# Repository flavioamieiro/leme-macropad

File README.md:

## Leme macropad

This is a macropad based on the RP2040 microcontroller meant to run QMK.

It currently is a handwired macropad using a raspberry Pi pico

The [README in the software directory](software/README.md) explains how to install QMK on a raspberry pi pico to support it.

The [leme_macropad](leme_macropad/) directory contains a first revision for custom hardware for it (which, unfortunately, currently doesn't work).

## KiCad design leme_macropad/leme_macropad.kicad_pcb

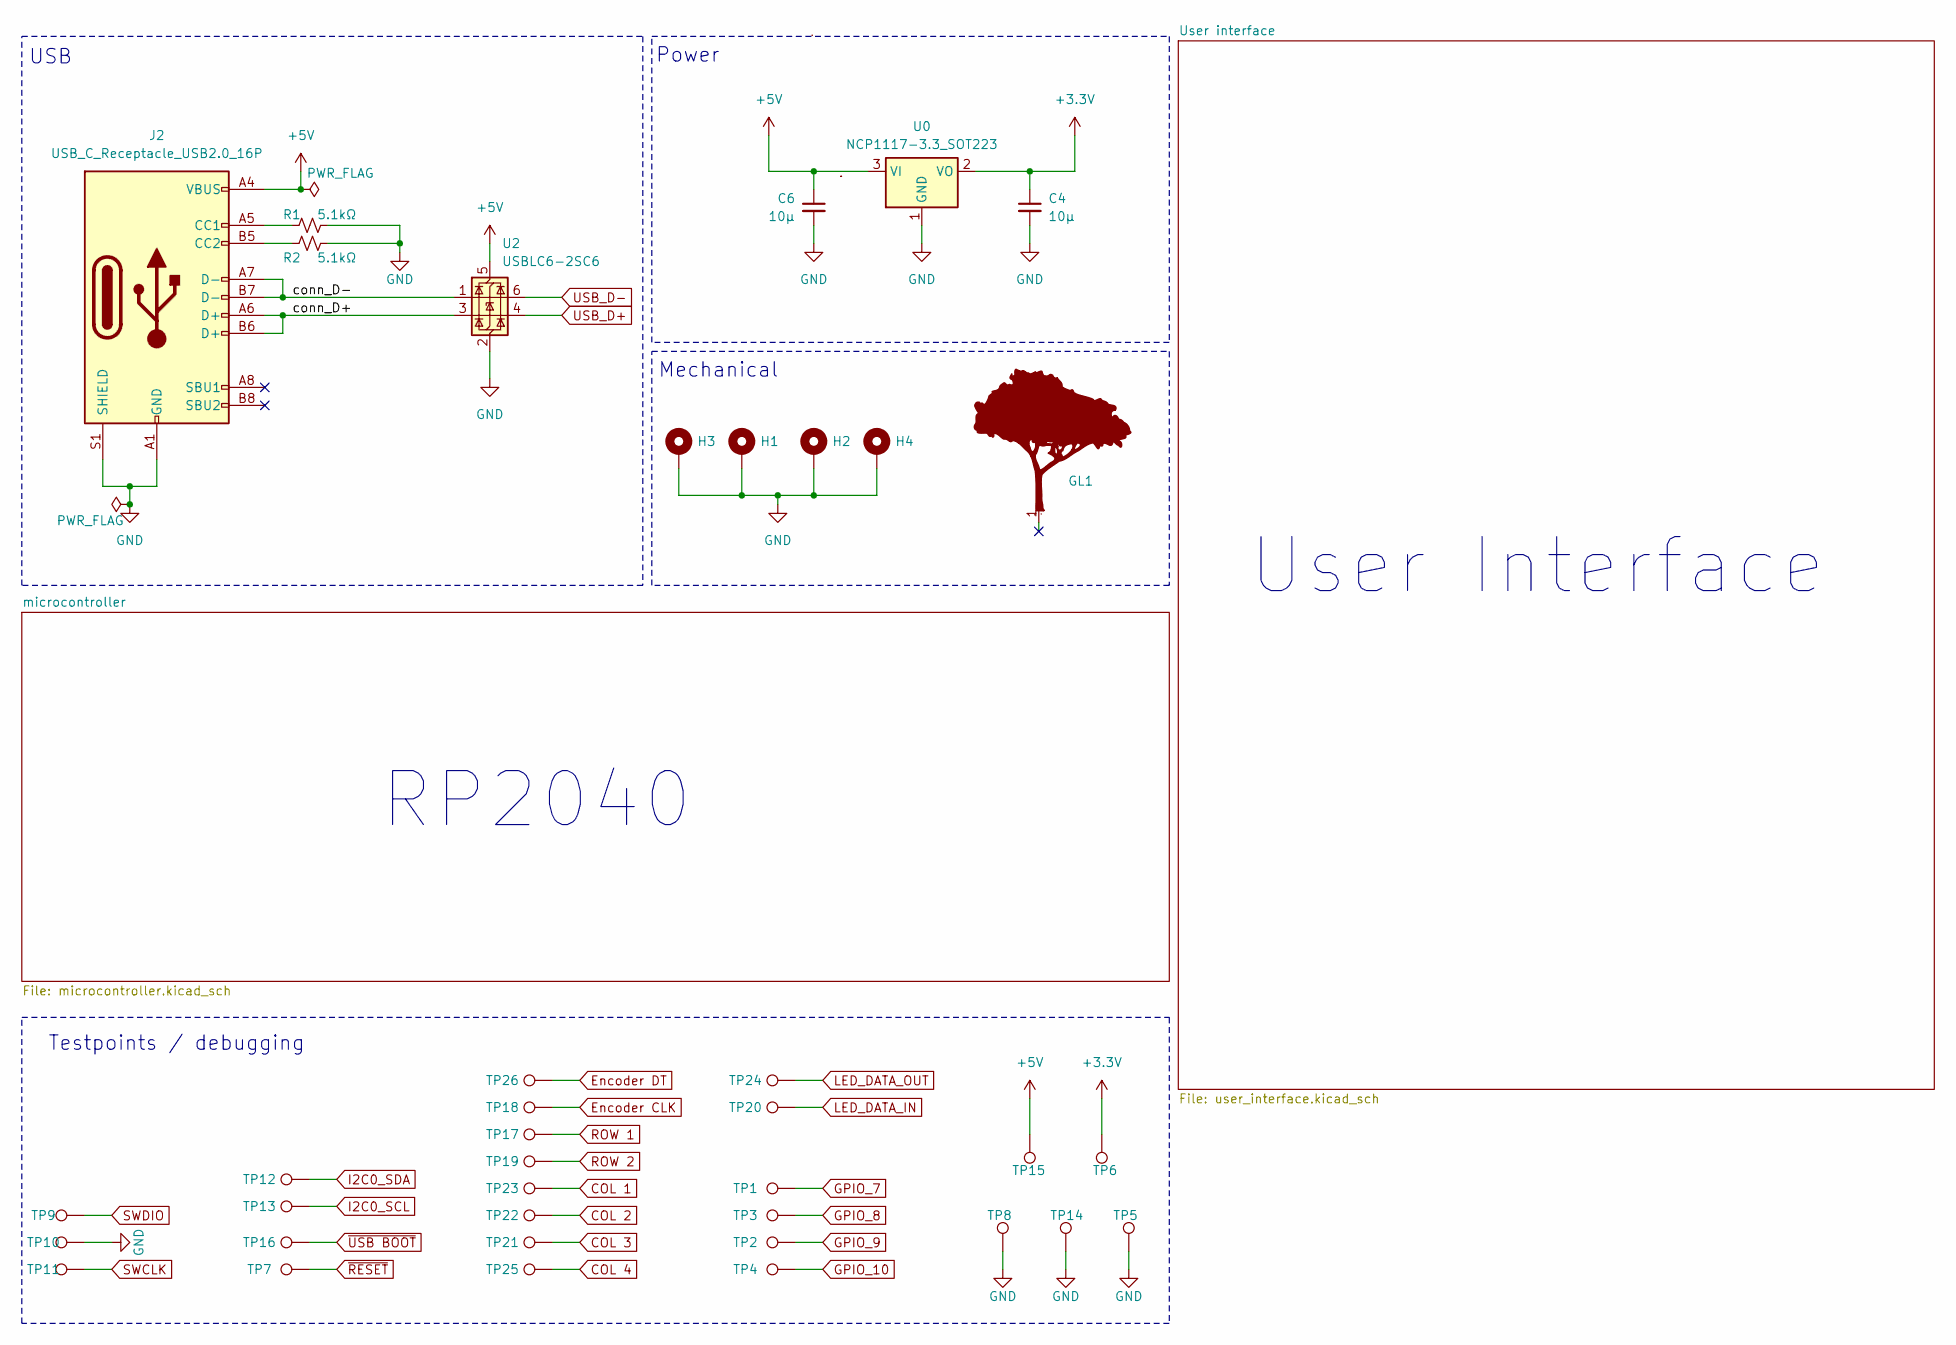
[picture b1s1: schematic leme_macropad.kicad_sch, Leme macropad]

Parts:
C4, C6: 10μ; C_0402_1005Metric_Pad0.74x0.62mm_HandSolder
GL1: ipe_logo
H1, H2, H3, H4: MountingHole_Pad; MountingHole_2.2mm_M2_Pad
J2: USB_C_Receptacle_USB2.0_16P; USB_C_Receptacle_GCT_USB4105-xx-A_16P_TopMnt_Horizontal
R1, R2: 5.1kΩ; R_0402_1005Metric_Pad0.72x0.64mm_HandSolder
TP1, TP2, TP3, TP4, TP5, TP6, TP7, TP8, TP9, TP10, TP11, TP12, TP13, TP14, TP15, TP16, TP17, TP18, TP19, TP20, TP21, TP22, TP23, TP24, TP25, TP26: TestPoint; TestPoint_Pad_D1.0mm
U0: NCP1117-3.3_SOT223; SOT-223-3_TabPin2
U2: USBLC6-2SC6; SOT-23-6

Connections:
+3.3V: C4.1, TP6.1, U0.2 (VO); also elsewhere on the board
+5V: C6.1, J2.A4 (VBUS), J2.A9 (VBUS), J2.B4 (VBUS), J2.B9 (VBUS), TP15.1, U0.3 (VI), U2.5 (VBUS); also elsewhere on the board
/conn_D+: J2.A6 (D+), J2.B6 (D+), U2.3 (I/O2)
/conn_D-: J2.A7 (D-), J2.B7 (D-), U2.1 (I/O1)
COL 1: TP23.1; also elsewhere on the board
COL 2: TP22.1; also elsewhere on the board
COL 3: TP21.1; also elsewhere on the board
COL 4: TP25.1; also elsewhere on the board
Encoder CLK: TP18.1; also elsewhere on the board
Encoder DT: TP26.1; also elsewhere on the board
GND: C4.2, C6.2, H1.1, H2.1, H3.1, H4.1, J2.A1 (GND), J2.A12 (GND), J2.B1 (GND), J2.B12 (GND), J2.S1 (SHIELD), R1.2, R2.2, TP5.1, TP8.1, TP10.1, TP14.1, U0.1 (GND), U2.2 (GND); also elsewhere on the board
GPIO_7: TP1.1; also elsewhere on the board
GPIO_8: TP3.1; also elsewhere on the board
GPIO_9: TP2.1; also elsewhere on the board
GPIO_10: TP4.1; also elsewhere on the board
I2C0_SCL: TP13.1; also elsewhere on the board
I2C0_SDA: TP12.1; also elsewhere on the board
LED_DATA_IN: TP20.1; also elsewhere on the board
LED_DATA_OUT: TP24.1; also elsewhere on the board
unnamed: J2.A5 (CC1), R1.1
unnamed: J2.B5 (CC2), R2.1
ROW 1: TP17.1; also elsewhere on the board
ROW 2: TP19.1; also elsewhere on the board
SWCLK: TP11.1; also elsewhere on the board
SWDIO: TP9.1; also elsewhere on the board
USB_D+: U2.4 (I/O2); also elsewhere on the board
USB_D-: U2.6 (I/O1); also elsewhere on the board
~RESET: TP7.1; also elsewhere on the board
~USB BOOT: TP16.1; also elsewhere on the board

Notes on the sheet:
Mechanical
User Interface
USB
RP2040
Testpoints / debugging
Power

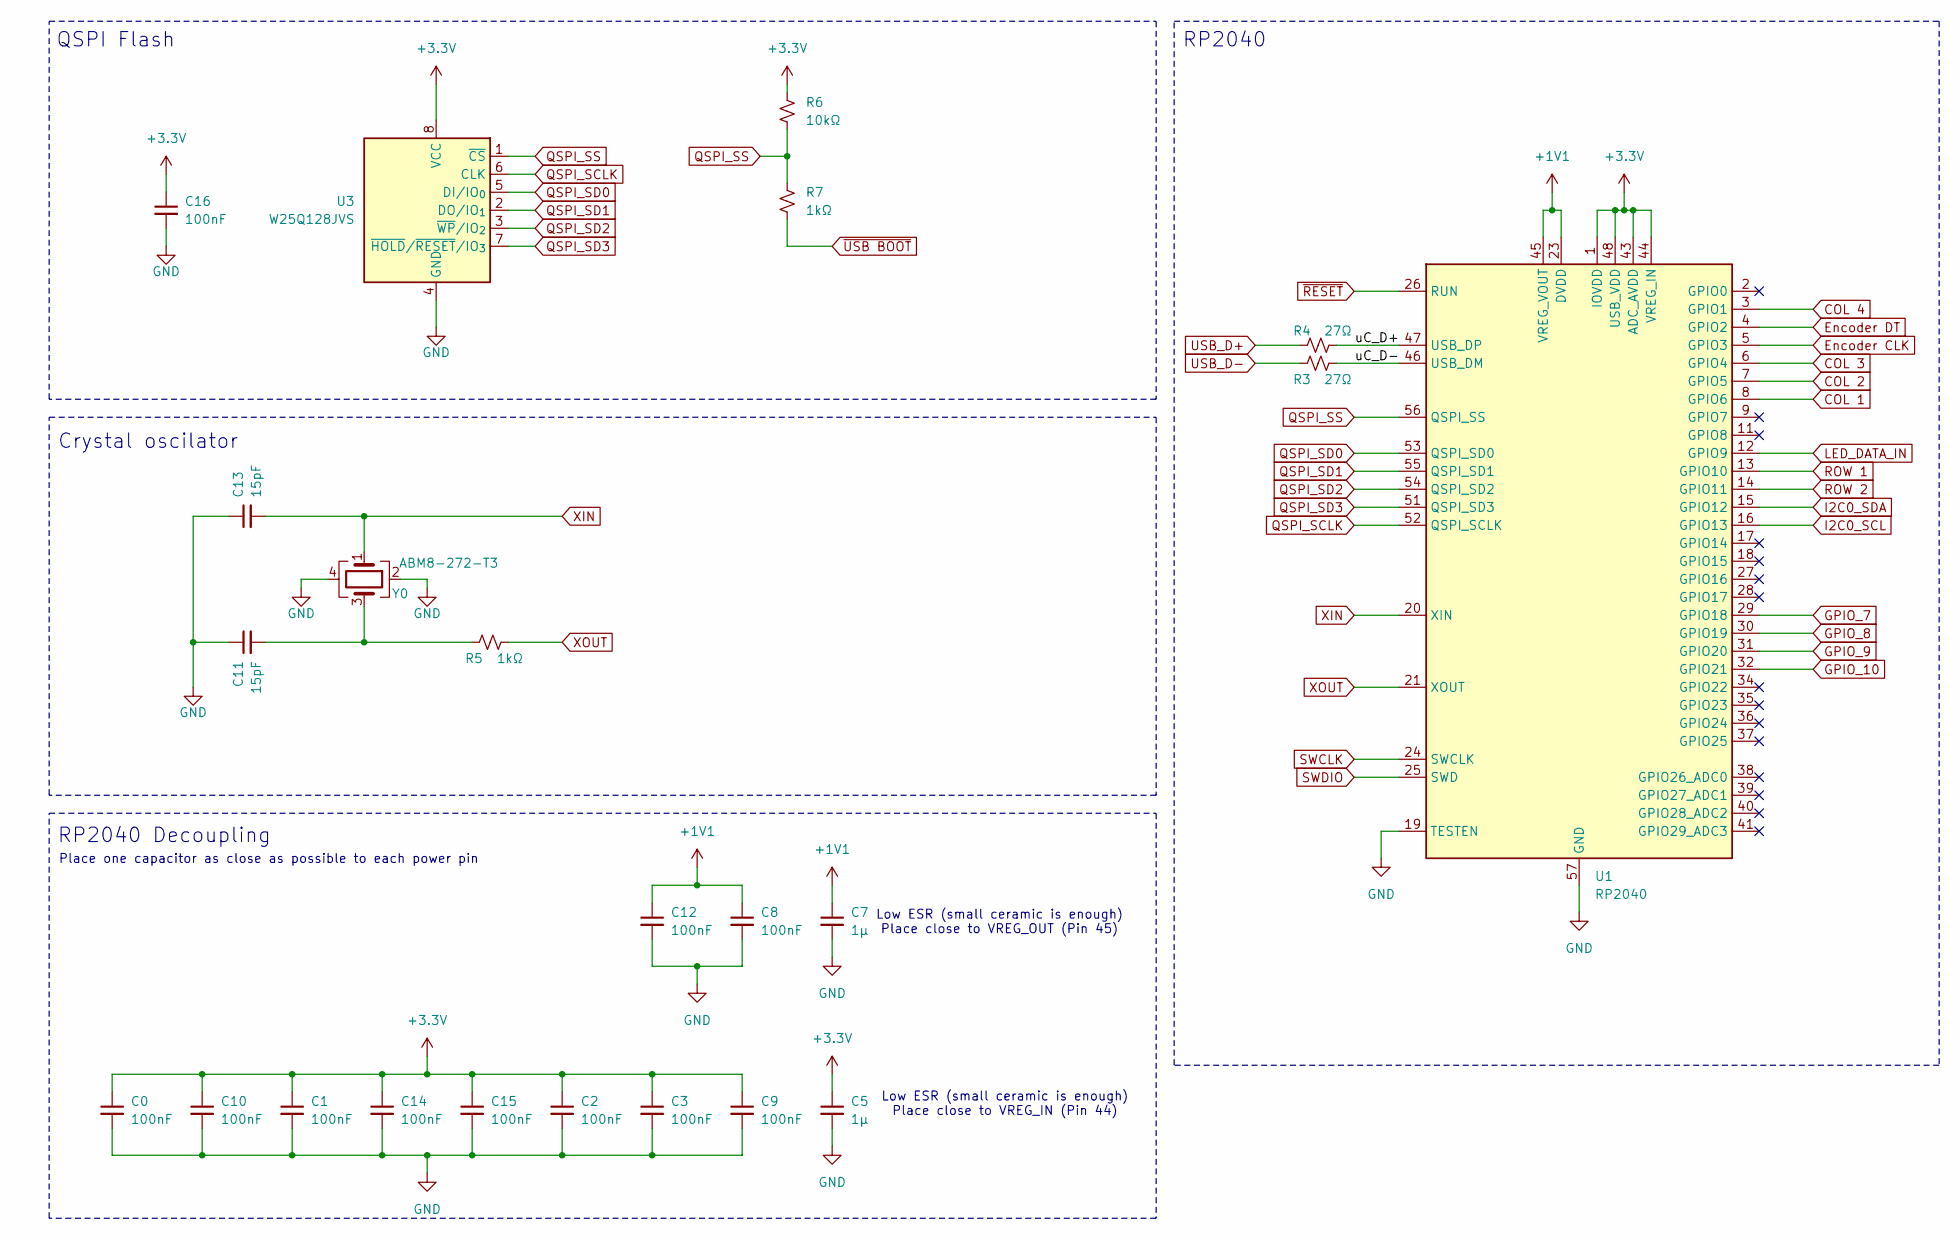
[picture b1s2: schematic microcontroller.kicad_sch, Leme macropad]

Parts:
C0, C1, C2, C3, C8, C9, C10, C12, C14, C15, C16: 100nF; C_0402_1005Metric_Pad0.74x0.62mm_HandSolder
C5, C7: 1μ; C_0402_1005Metric_Pad0.74x0.62mm_HandSolder
C11, C13: 15pF; C_0402_1005Metric_Pad0.74x0.62mm_HandSolder
R3, R4: 27Ω; R_0402_1005Metric_Pad0.72x0.64mm_HandSolder
R5, R7: 1kΩ; R_0402_1005Metric_Pad0.72x0.64mm_HandSolder
R6: 10kΩ; R_0402_1005Metric_Pad0.72x0.64mm_HandSolder
U1: RP2040; QFN-56-1EP_7x7mm_P0.4mm_EP3.2x3.2mm
U3: W25Q128JVS; SOIC-8_5.3x5.3mm_P1.27mm
Y0: ABM8-272-T3; Crystal_SMD_3225-4Pin_3.2x2.5mm

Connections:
+1V1: C7.1, C8.1, C12.1, U1.23 (DVDD), U1.45 (VREG_VOUT), U1.50 (DVDD)
+3.3V: C0.1, C1.1, C2.1, C3.1, C5.1, C9.1, C10.1, C14.1, C15.1, C16.1, R6.2, U1.1 (IOVDD), U1.10 (IOVDD), U1.22 (IOVDD), U1.33 (IOVDD), U1.42 (IOVDD), U1.43 (ADC_AVDD), U1.44 (VREG_IN), U1.48 (USB_VDD), U1.49 (IOVDD), U3.8 (VCC); also elsewhere on the board
/microcontroller/uC_D+: R4.2, U1.47 (USB_DP)
/microcontroller/uC_D-: R3.2, U1.46 (USB_DM)
COL 1: U1.8 (GPIO6); also elsewhere on the board
COL 2: U1.7 (GPIO5); also elsewhere on the board
COL 3: U1.6 (GPIO4); also elsewhere on the board
COL 4: U1.3 (GPIO1); also elsewhere on the board
Encoder CLK: U1.5 (GPIO3); also elsewhere on the board
Encoder DT: U1.4 (GPIO2); also elsewhere on the board
GND: C0.2, C1.2, C2.2, C3.2, C5.2, C7.2, C8.2, C9.2, C10.2, C11.1, C12.2, C13.1, C14.2, C15.2, C16.2, U1.19 (TESTEN), U1.57 (GND), U3.4 (GND), Y0.2, Y0.4; also elsewhere on the board
GPIO_7: U1.29 (GPIO18); also elsewhere on the board
GPIO_8: U1.30 (GPIO19); also elsewhere on the board
GPIO_9: U1.31 (GPIO20); also elsewhere on the board
GPIO_10: U1.32 (GPIO21); also elsewhere on the board
I2C0_SCL: U1.16 (GPIO13); also elsewhere on the board
I2C0_SDA: U1.15 (GPIO12); also elsewhere on the board
LED_DATA_IN: U1.12 (GPIO9); also elsewhere on the board
unnamed: C11.2, R5.1, Y0.3
QSPI_SCLK: U1.52 (QSPI_SCLK), U3.6 (CLK)
QSPI_SD0: U1.53 (QSPI_SD0), U3.5 (DI/IO_{0})
QSPI_SD1: U1.55 (QSPI_SD1), U3.2 (DO/IO_{1})
QSPI_SD2: U1.54 (QSPI_SD2), U3.3 (~WP/IO_{2})
QSPI_SD3: U1.51 (QSPI_SD3), U3.7 (~HOLD/~RESET/IO_{3})
QSPI_SS: R6.1, R7.2, U1.56 (QSPI_SS), U3.1 (~CS)
ROW 1: U1.13 (GPIO10); also elsewhere on the board
ROW 2: U1.14 (GPIO11); also elsewhere on the board
SWCLK: U1.24 (SWCLK); also elsewhere on the board
SWDIO: U1.25 (SWD); also elsewhere on the board
USB_D+: R4.1; also elsewhere on the board
USB_D-: R3.1; also elsewhere on the board
XIN: C13.2, U1.20 (XIN), Y0.1
XOUT: R5.2, U1.21 (XOUT)
~RESET: U1.26 (RUN); also elsewhere on the board
~USB BOOT: R7.1; also elsewhere on the board

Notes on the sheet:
RP2040 Decoupling
Place one capacitor as close as possible to each power pin
QSPI Flash
RP2040
Low ESR (small ceramic is enough) Place close to VREG_OUT (Pin 45)
Low ESR (small ceramic is enough) Place close to VREG_IN (Pin 44)
Crystal oscilator

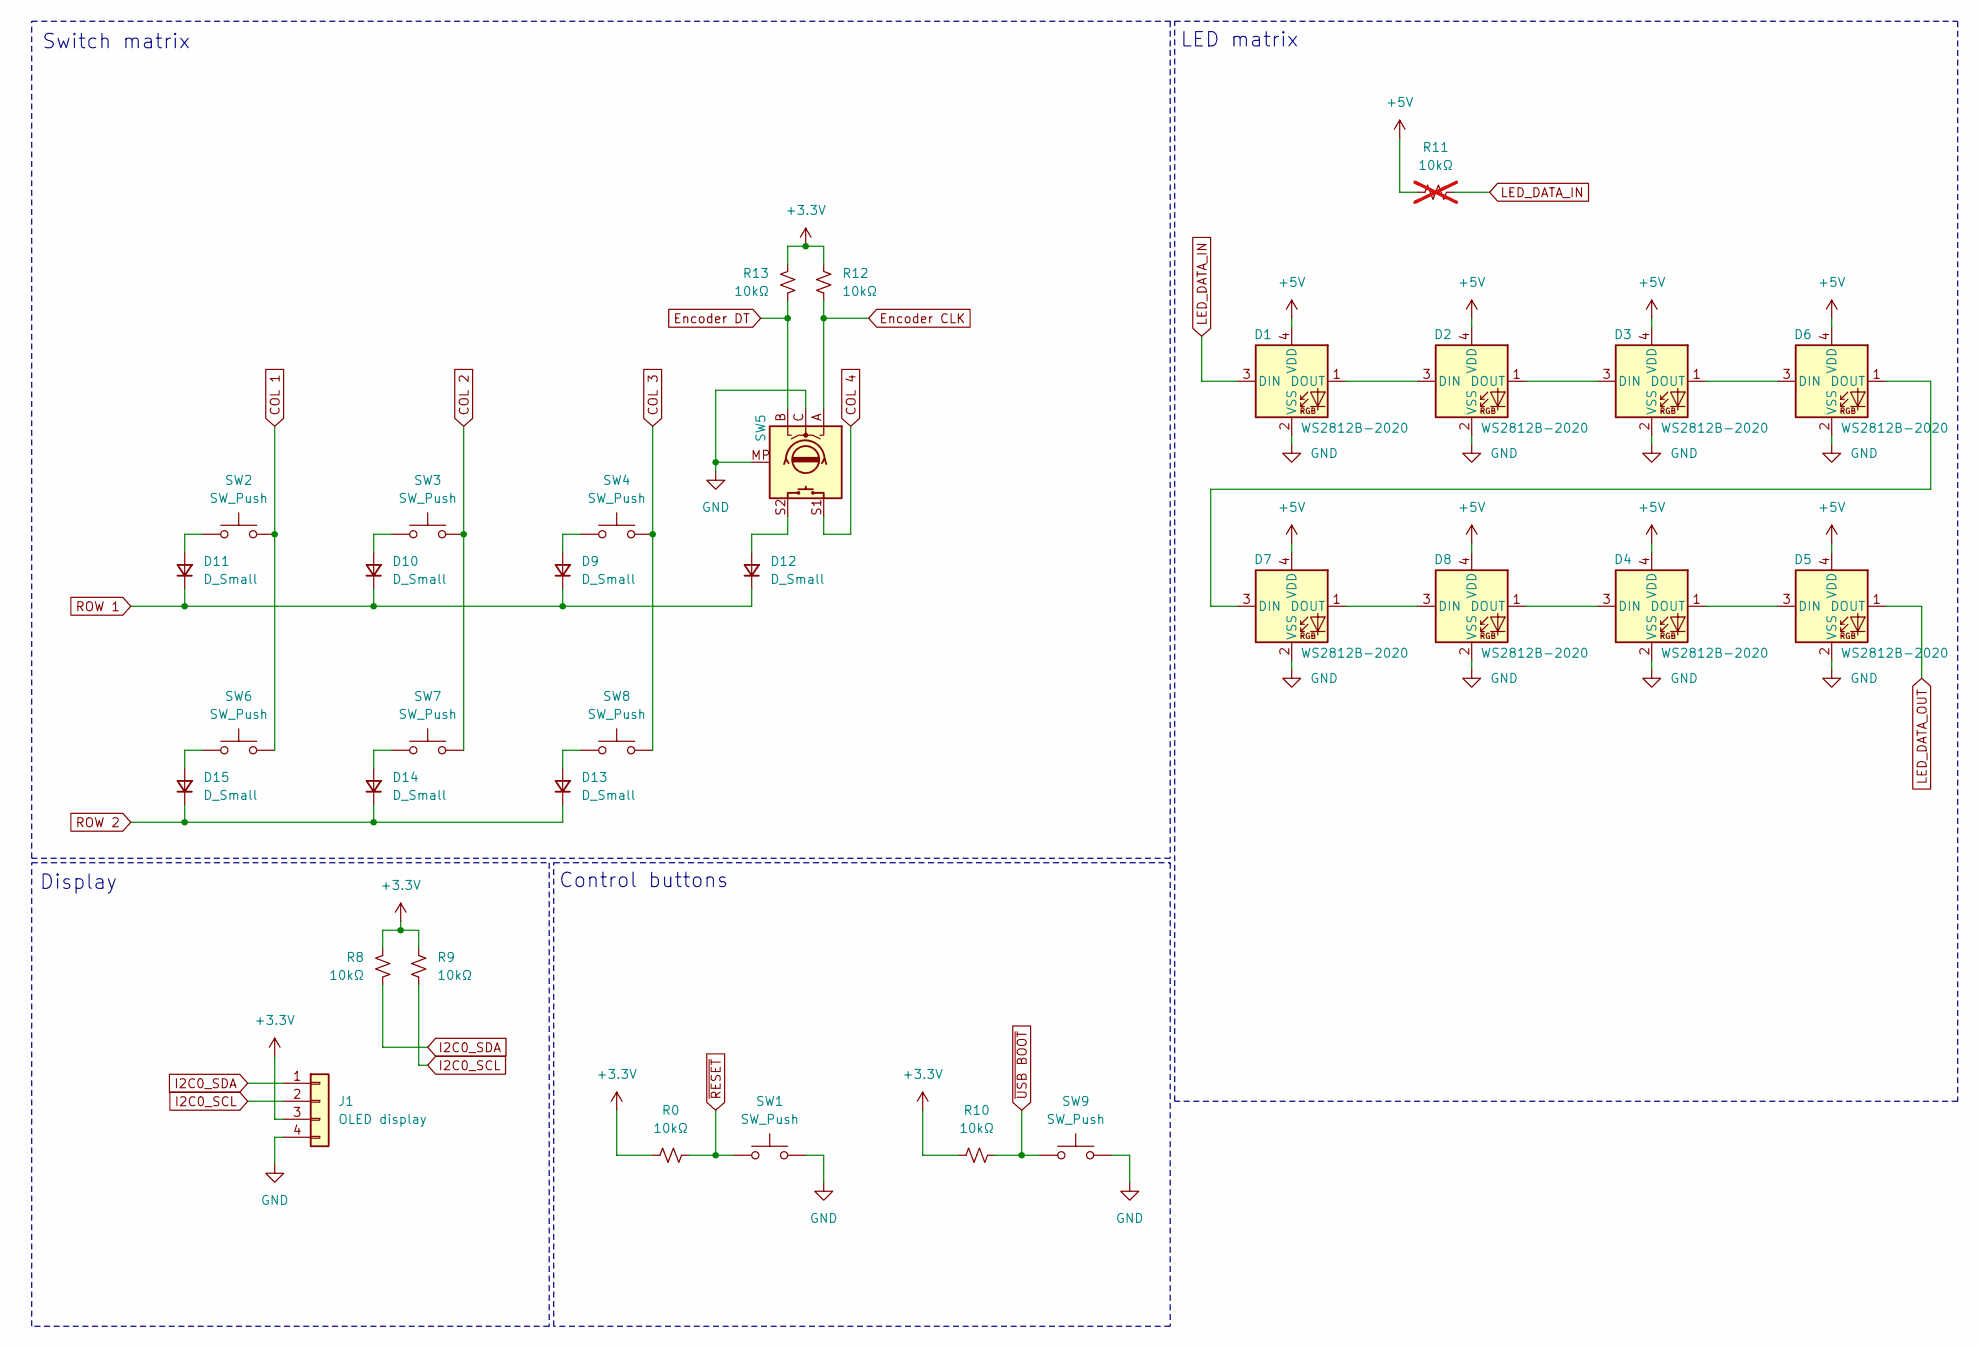
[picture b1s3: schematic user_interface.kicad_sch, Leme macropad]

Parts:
D1, D2, D3, D4, D5, D6, D7, D8: WS2812B-2020; LED_WS2812B-2020_PLCC4_2.0x2.0mm
D9, D10, D11, D12, D13, D14, D15: D_Small; D_SOD-123
J1: OLED display; PinHeader_1x04_P2.54mm_Vertical
R0, R8, R9, R10, R12, R13: 10kΩ; R_0402_1005Metric_Pad0.72x0.64mm_HandSolder
R11: 10kΩ; R_0402_1005Metric_Pad0.72x0.64mm_HandSolder; not fitted
SW1, SW9: SW_Push; CK_PTS636_SK43_SMTR_LFS
SW2, SW3, SW4, SW6, SW7, SW8: SW_Push; SW_Hotswap_Kailh_Choc_V1V2_1.00u
SW5: RotaryEncoder_Switch; RotaryEncoder_Alps_EC11E-Switch_Vertical_H20mm

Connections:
+3.3V: J1.3, R0.1, R8.2, R9.2, R10.1, R12.2, R13.2; also elsewhere on the board
+5V: D1.4 (VDD), D2.4 (VDD), D3.4 (VDD), D4.4 (VDD), D5.4 (VDD), D6.4 (VDD), D7.4 (VDD), D8.4 (VDD), R11.1; also elsewhere on the board
COL 1: SW2.2, SW6.2; also elsewhere on the board
COL 2: SW3.2, SW7.2; also elsewhere on the board
COL 3: SW4.2, SW8.2; also elsewhere on the board
COL 4: SW5.S1; also elsewhere on the board
Encoder CLK: R12.1, SW5.A; also elsewhere on the board
Encoder DT: R13.1, SW5.B; also elsewhere on the board
GND: D1.2 (VSS), D2.2 (VSS), D3.2 (VSS), D4.2 (VSS), D5.2 (VSS), D6.2 (VSS), D7.2 (VSS), D8.2 (VSS), J1.4, SW1.2, SW5.C, SW5.MP, SW9.2; also elsewhere on the board
I2C0_SCL: J1.2, R9.1; also elsewhere on the board
I2C0_SDA: J1.1, R8.1; also elsewhere on the board
LED_DATA_IN: D1.3 (DIN), R11.2; also elsewhere on the board
LED_DATA_OUT: D5.1 (DOUT); also elsewhere on the board
unnamed: D1.1 (DOUT), D2.3 (DIN)
unnamed: D2.1 (DOUT), D3.3 (DIN)
unnamed: D3.1 (DOUT), D6.3 (DIN)
unnamed: D4.3 (DIN), D8.1 (DOUT)
unnamed: D4.1 (DOUT), D5.3 (DIN)
unnamed: D6.1 (DOUT), D7.3 (DIN)
unnamed: D7.1 (DOUT), D8.3 (DIN)
unnamed: D9.2 (A), SW4.1
unnamed: D10.2 (A), SW3.1
unnamed: D11.2 (A), SW2.1
unnamed: D12.2 (A), SW5.S2
unnamed: D13.2 (A), SW8.1
unnamed: D14.2 (A), SW7.1
unnamed: D15.2 (A), SW6.1
ROW 1: D9.1 (K), D10.1 (K), D11.1 (K), D12.1 (K); also elsewhere on the board
ROW 2: D13.1 (K), D14.1 (K), D15.1 (K); also elsewhere on the board
~RESET: R0.2, SW1.1; also elsewhere on the board
~USB BOOT: R10.2, SW9.1; also elsewhere on the board

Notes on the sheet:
Control buttons
Switch matrix
LED matrix
Display

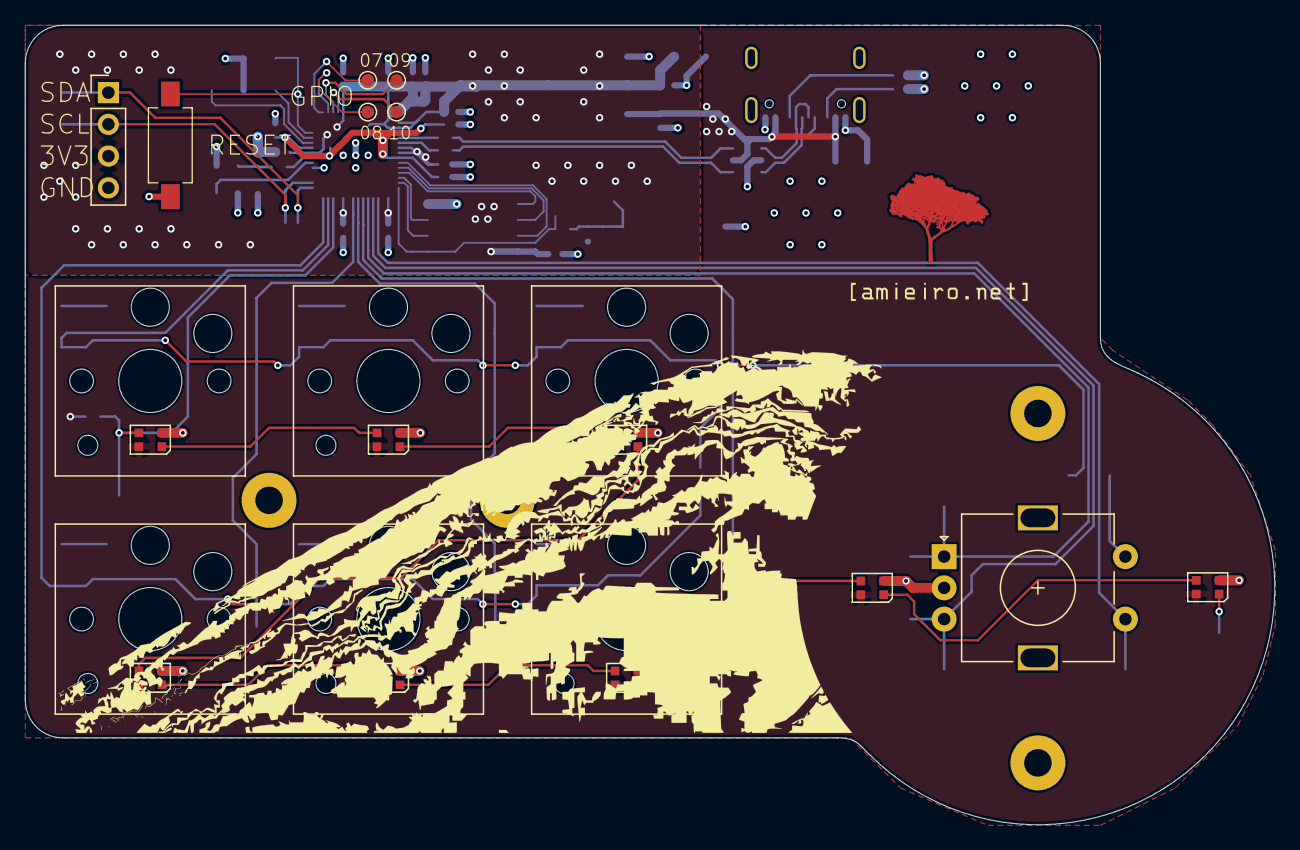
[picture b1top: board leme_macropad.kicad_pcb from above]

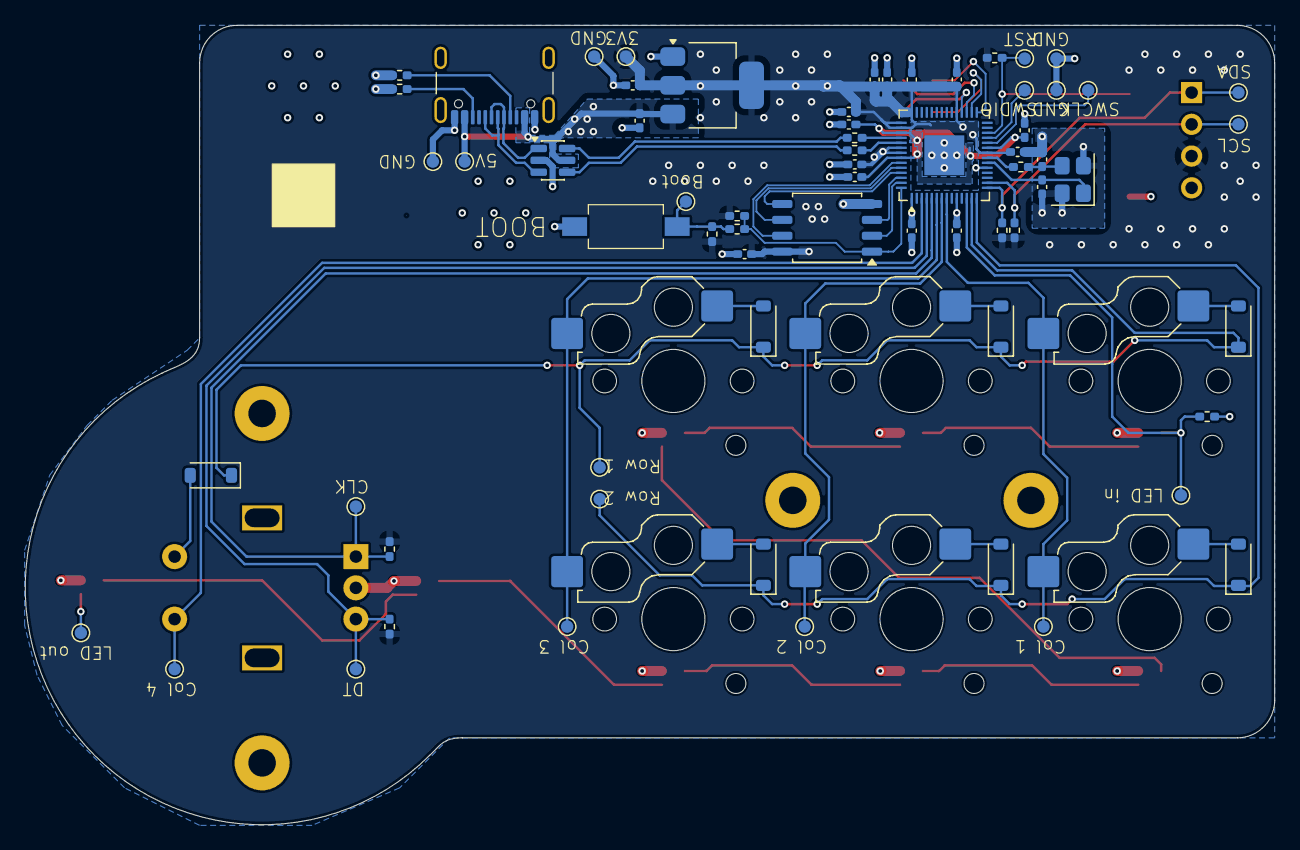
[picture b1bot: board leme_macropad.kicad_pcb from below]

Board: 4 copper layers, 99.9 x 63.9 mm, 94 parts (67 on the bottom side), 55 nets.

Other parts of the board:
Ref**: Val**; sea

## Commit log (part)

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2024-07-22 Adds first version of the code for a breadboad single button prototype
    This first prototype includes a rotary encoder and an i2c OLED display
    but only one single button. The idea was to test one of each component.
2024-07-26 Adds start of schematics and update code for perfboard prototype
    This schematics is limited only to what is in the perfboard. The code
    now also reflects the way the perfboard is wired.
2024-08-01 Adds Freecad project with a first case design
    This case design is meant to test the form factor. It doesn't fit the
    current electronics, since they were prototyped in a rather large
    perfboard. In it's current form, it can't be hardwired either, since
    there is no space for the Pi Pico inside.
2024-08-09 Finished first version of the case design
    This includes a bottom with a space for the raspberry pi pico.
    There are a few issues, mainly there's not enough space for all the
    wires (with JST connectors) I used in the prototype because one of the
    connectors hits the back of the display.
2024-08-12 Adds second layer with encoder as mouse scroll
2024-08-12 Changes col pins order for new handwired prototype
2025-04-20 Updates kicad project to kicad version 9.0
2025-04-21 Changes firmware to use QMK instead of KMK
    This QMK firmware is still very limited in comparrison to what was
    available with KMK.
    * It still has only one layer
    * The rotary encoder pushbutton doesn't work yet
    * The display is not yet included
2025-04-21 Enables ENCODER_MAP in keymap
    This allows us to describe keycode mappings for encoders in the same
    way we do for the keyboard matrix.
2025-04-21 Cleans the readme file for the keyboard
2025-04-21 Fixes copyright statement in keymaps.c
2025-04-21 Adds second layer to the macropad
    This has the same keycodes used in the previous KMK firmware, which
    means the second layer is only useful to change the rotary encoder into
    a mouse wheel instead of a volume knob. This layer should be expanded
    for more navigation helpers, and this is why I named it as `NAVIGATION`.
2025-04-21 Explains how to flash the software in README.md
2025-04-24 Adds support for OLED display
    This display uses I2C0 in the RPi with SDA on GP4 and SCL on GP5
2025-04-24 Fixes whitespace in rules.mk
2025-04-24 Adds scrolling and fade out to OLED screen
    The scrolling helps avoid burn-in on the screen, and the fade out just
    looks better.
    This commit also decreases the time it takes to clear the screen.
2025-04-24 Adds shortcut key in second layer to put the keyboard in bootloader mode
    This makes it much easier to test code, but should probably be removed
    later.
2025-05-13 Renames kicad project
2025-05-16 Uses rotary encoder instead of module and includes switch in matrix
    The way QMK handles rotary encoder push buttons is to include it in the
    switch matrix, which means I needed to add another column. Since this
    opens space for an extra switch, I added it here, but it doesn't need to
    be a mechanical switch as the others. We can keep the same 3x2 layout of
    the main keys.
    Using the encoder instead of a module is the right way to go. The
2025-05-16 Removes old Pi Pico library from the project
    We can use the official Kicad symbol and footprint for the RP2040 we'll
    use.
2025-05-16 Replaces Pi pico with a RP2040
    This is much better for our purposes. It gives us more control, uses
    much less space on the PCB and allows us to use a USB-C connector.
    All the components around the RP2040 are the ones recommended in the
    RP2040 hardware design guide. They not only are recommended, but also
    readily available and easy enough to use.
2025-05-23 Moves user interface to it's own hierarchical sheet
2025-05-23 Adds RGB LED matrix
    There's only one per switch for now.
2025-05-23 Adds testpoints to a lot of signals
2025-05-23 Adds testpoints to some free GPIOs
    It doesn't hurt to have them broken out if we need it.
2025-05-23 Re-annotates schematics
2025-05-23 Reorganizes testpoints in schematics
2025-05-23 Adds footprint for CK PTS636 SK43 SMTR LFS pushbutton
2025-05-29 Adds M2 mounting holes to schematics
    The mounting holes are pads and connected to ground.
2025-05-29 Adds logo to schematics
    This includes a symbol and a footprint. The logo is a pad, connected to
    ground.
2025-05-29 Ignores *bak and *.lck in git
2025-05-29 Uses rotary encoder symbol with mounting pin
    The rotary switch we'll use has mounting pins that can be soldered.
    Since they're connected to the chassis, they're now connected to ground
    in the schematics.
    This change fixes a warning when importing the schematics to the PCB
    editor.
2025-05-29 Moves logo footprint to the front copper layer
    We can always flip it in the board if we want. Being in the front is a
    better default.
2025-05-29 Clears PCB in PCB editor
2025-05-29 Defines project defaults for PCB editor
    This includes pre-defined trace (and diff pair) widths, some DRC
    constraints and a 19.05mm grid to make it easier to position standard 1U
    switches.
2025-05-29 Adds edge cuts layer
    This was drawn based on a DXF exported from the bottom side of the
    current case.
2025-05-29 Adds components from schematics on PCB
2025-05-29 Positions rotary encoder relative to the knob
2025-05-29 Creates mechanical switch grouping with correct spacing between them
    The position is definitely not final, but at least they should be
    correct in relation to each other.
2025-05-30 Reduces PCB size to fit in the 100mmx100mm promotional price in JLCPCB
    The cost - including shipping and taxes - for the original dimensions
    would be too high, specially for a first revision. I might want to go
    back to the original dimensions later, but for now we'll keep it
    smaller, even at the expense of a bit of comfort in use.
2025-05-30 First placement of components the user interacts with
    This does not yet include the LEDs, though.
2025-06-27 Moves switch on top layer to be hidden under the display
2025-06-27 Brings RP2040 and components around it closer to where they'll be
2025-06-27 Moves mounting point H2
    This should open more space for the layout of the microcontroller and
    everything else, while also hiding the only visible mounting whole and
    securing even more the rotary encoder.
2025-06-27 Removes SW8
    This button was there just to complete the matrix but we have no use for
    it. It would only make things harder to organize.
2025-06-30 First draft of the layout for the crystal oscillator
    This is not looking very good, but gives an idea of where the crystal
    should be. This might also be a good indication that we need to change
    the passives around the RP2040 to 0402, since 0603 are looking quite big
    right now.
2025-06-30 Changes resistors and capacitors to 0402
    This should make it much easier to route things and to comply with the
    signal integrity needs of some parts of the circuit.
2025-06-30 Reorganizes crystal oscillator after changing passives to 0402
2025-06-30 Swaps USB pins on SRV05 to make routing easier
2025-09-19 Replaces SRV05 with USBLC6 for ESD protection
    The USBLC6 is not only built specifically to protect USB data lines, but
    is also cheaper than the SRV05.
2025-09-19 Routes USB data lines
    Yeah, it's not good, but it is what it is for now.
2025-09-19 Adds ground plane in inner layers
2025-09-19 Adds vias to ground for components that were already routed
2025-09-22 Moves USB TVS diode a bit further down.
2025-09-22 Routes QSPI flash
2025-09-22 Brings back inner GND planes
    For some reason they were deleted in the last commit.
2025-09-22 Adds 3v3 plane to the top layer
2025-09-22 Roughly positions logo
2025-09-22 Routes ws2812 LEDs
2025-09-22 Routes i2c lines to the display
2025-09-22 Routes reset button
2025-09-24 Use smaller testpoint pads
    We have quite a few of them, and at 2mm it was impossible to space them
    0.1" apart.
2025-09-24 Removes unused tespoints
2025-09-24 Reassigns designators based on component location on the PCB
    Kicad 6 has a tool for that: geographical reannotate.
2025-09-24 Small adjustments
2025-09-26 Deletes all tracks and vias to start from scratch
    This also removes the 3v3 and 5V planes.
2025-09-26 Separates out logical groups of components so we can reorganize them
2025-09-26 Moves screw hole to open more space for routing
    This will also add more support to the buttons, albeit at the expense of
    losing some under de display connect. Because the display will likely
    not be connected and disconnected often, this should be ok.
2025-09-26 Routes RP2040 power
    This is basically a copy of the reference RP2040 design. Ground
    connections are still missing, even in the center pad, mainly because
    this footprint doesn't include vias.
2025-09-26 Routes crystal oscillator
2025-09-26 Routes USB diffpair
2025-09-26 Routes QSPI data lines
2025-09-26 Moves USB connector to allow for more space for the power regulator
    The connector was in the midpoint of the board (considering the
    right-most part of the knob). Now it's a bit offset to the right.
    This is less than ideal, but will make life much easier.
2025-09-26 Routes power regulator
2025-09-26 Routes SWD debug signals and reset
    This required moving the decoupling capacitor for 1.1v.
2025-09-26 Routes power testpoints
2025-09-29 Adds i2c pull-up resistors that were missing (!)
2025-09-30 Moves SDA/SCL i2c pins to make it easier to route
    This also required moving the encoder pins, which will also make them
    easier to route with this placement of the RP2040.
    This commit also changes the configuration for QMK to use the new pins.
2025-10-01 Changes the matrix pins hoping it will make them easier to route
2025-10-03 Routes rows, columns and encoder
2025-10-03 Reorders ws2812 LEDs
2025-10-03 Changes ws2812 data pin
2025-10-03 Routes i2c lines
2025-10-03 Creates 3.3V and 5V planes
2025-10-03 Routes last missing items
2025-10-03 Fixes placement of the logo designator on schematics
2025-10-03 Adds pull-up resistor footprint (component marked as DNP) to the LED data line
    QMK has a open-drain WS2812 driver[1], which we can potentially use to
    drive the LEDs at 5V. The issue is that, in theory, the RP2040 is not 5V
    tolerant, and the QMK docs are very specific about this needing to be
    the case. That's why the component is marked as "Do Not Populate", and
    we'll leave the footprint there for experimentation.
    [1]: https://docs.qmk.fm/drivers/ws2812#open-drain-circuit
2025-10-03 Adds stitching vias to 3V3, 5V and GND
2025-10-04 Geographically reanotates component designators
2025-10-04 Updates logo
2025-10-04 Adds labels to all testpoints
2025-10-05 Adds new footprint with a svg trace of the Leme sea
    This was generated in inkscape using github.com/badgeek/svg2shenzhen
2025-10-05 Adds some missing labels
2025-10-05 Changes NET for some 5V stitching vias that could only connect on one layer
2025-10-05 Updates U3 footprint from layer
2025-10-05 Removes cosmetic silkscreen to make it easier to see DRC violations that matter
2025-10-06 Excludes DRC violations for LEDs under Switches
    These LEDs will not be populated at first and the switches actually have
    enough space for them, but the footprint I'm using doesn't allow for
    this space in it's courtyard rules.
2025-10-06 Excludes DRC violations for GCT USB4105 connector
    This error is in the Kicad PCB itself, and I've used this connector with
    the same footprint in other boards with no issues.
2025-10-06 Brings back cosmetic silkscreen
2025-10-06 Adds placeholder for JLCPCB 2D barcode
2025-10-06 Also adds 3D models of the actual switches
    The footprint I'm using is for the hotswap sockets, so it makes sense
    that only the model for the sockets is there. I did, however, want the
    actual switches to show in the 3D render, so I added them to the
    footprints manually.
2025-10-09 Updates PCBs from library
    They started triggering DRC errors, probably because of kicad symbols
    update.
